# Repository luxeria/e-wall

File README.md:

e-wall
======

Steuerung e-wall

Die E-Wall ist eine Wand bestehend aus 12 Mainboards. 
Wenn Personen vor der Wand durchlaufen, soll darauf reagiert werden. 

Die Messung der Distanz erfolgt dabei über Ultraschall. 
Die Lüfter und LEDs werden mit einem Schieberegister angesteuert.

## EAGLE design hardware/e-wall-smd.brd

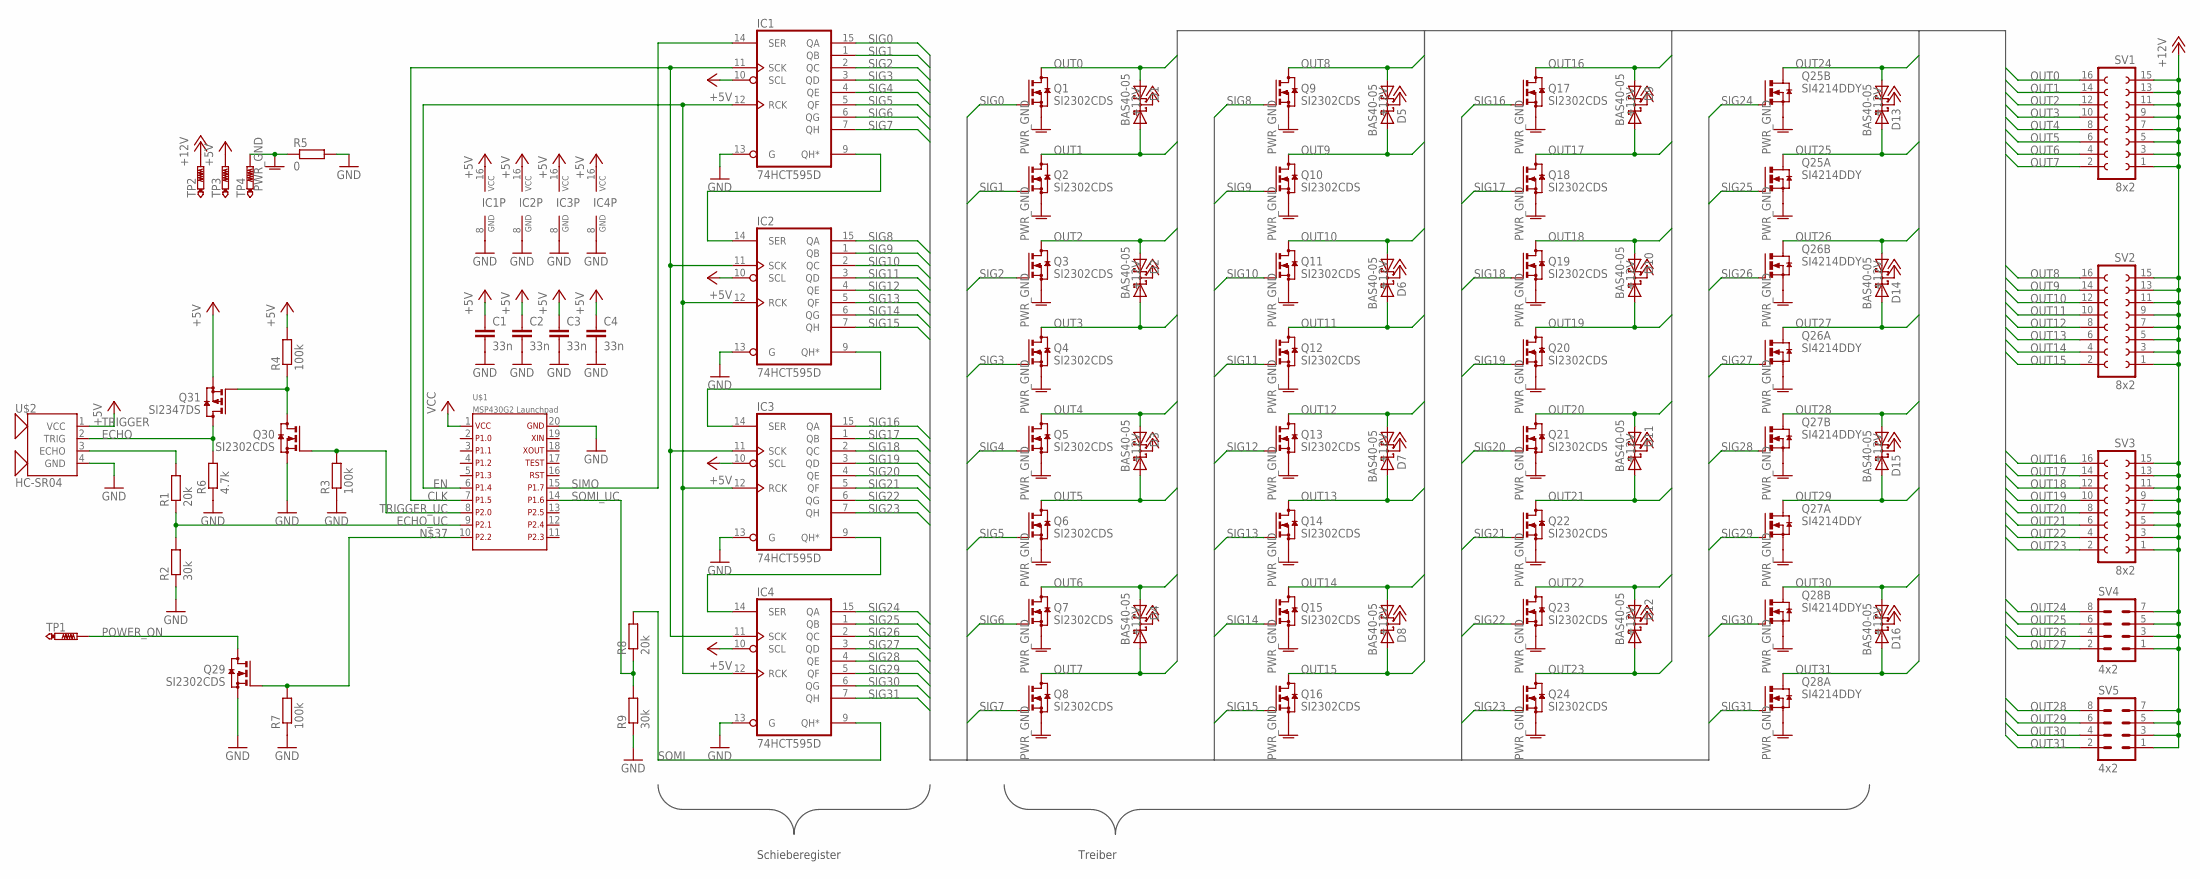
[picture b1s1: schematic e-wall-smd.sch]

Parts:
C1, C2, C3, C4: 33n; C1206
D1, D2, D3, D4, D5, D6, D7, D8, D9, D10, D11, D12, D13, D14, D15, D16: BAS40-05; SOT23
IC1, IC2, IC3, IC4: 74HCT595D; SO16
Q1, Q2, Q3, Q4, Q5, Q6, Q7, Q8, Q9, Q10, Q11, Q12, Q13, Q14, Q15, Q16, Q17, Q18, Q19, Q20, Q21, Q22, Q23, Q24, Q29, Q30: SI2302CDS; SOT23
Q25, Q26, Q27, Q28: SI4214DDY; SO-08
Q31: SI2347DS; SOT23
R1, R8: 20k; R1206
R2, R9: 30k; R1206
R3, R4, R7: 100k; R1206
R5: 0; R1206
R6: 4.7k; R1206
SV1, SV2, SV3: 8x2; FE08-2
SV4, SV5: 4x2; MA04-2
TP1, TP2, TP3, TP4: PTR1PAD1-20; P1-20
U$1: MSP430G2 Launchpad; MSP430LAUNCHPAD_BASIC
U$2: HC-SR04

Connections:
+5V: C1.1, C2.1, C3.1, C4.1, IC1.10 (SCL), IC1.16 (VCC), IC2.10 (SCL), IC2.16 (VCC), IC3.10 (SCL), IC3.16 (VCC), IC4.10 (SCL), IC4.16 (VCC), Q31.2 (S), R4.2, TP3.TP, U$2.1 (VCC)
+12V: D1.3 (C), D2.3 (C), D3.3 (C), D4.3 (C), D5.3 (C), D6.3 (C), D7.3 (C), D8.3 (C), D9.3 (C), D10.3 (C), D11.3 (C), D12.3 (C), D13.3 (C), D14.3 (C), D15.3 (C), D16.3 (C), SV1.1, SV1.3, SV1.5, SV1.7, SV1.9, SV1.11, SV1.13, SV1.15, SV2.1, SV2.3, SV2.5, SV2.7, SV2.9, SV2.11, SV2.13, SV2.15, SV3.1, SV3.3, SV3.5, SV3.7, SV3.9, SV3.11, SV3.13, SV3.15, SV4.1, SV4.3, SV4.5, SV4.7, SV5.1, SV5.3, SV5.5, SV5.7, TP2.TP
CLK: IC1.11 (SCK), IC2.11 (SCK), IC3.11 (SCK), IC4.11 (SCK), U$1.7
ECHO: R1.2, U$2.3 (ECHO)
ECHO_UC: R1.1, R2.2, U$1.9
EN: IC1.12 (RCK), IC2.12 (RCK), IC3.12 (RCK), IC4.12 (RCK), U$1.6
GND: C1.2, C2.2, C3.2, C4.2, IC1.8 (GND), IC1.13 (G), IC2.8 (GND), IC2.13 (G), IC3.8 (GND), IC3.13 (G), IC4.8 (GND), IC4.13 (G), Q29.2 (S), Q30.2 (S), R2.1, R3.1, R5.2, R6.1, R7.1, R9.1, U$1.20, U$2.4 (GND)
unnamed: IC1.9 (QH*), IC2.14 (SER)
unnamed: IC2.9 (QH*), IC3.14 (SER)
unnamed: IC3.9 (QH*), IC4.14 (SER)
unnamed: Q30.3 (D), Q31.1 (G), R4.1
unnamed: Q29.1 (G), R7.2, U$1.10
OUT0: D1.2 (A2), Q1.3 (D), SV1.16
OUT1: D1.1 (A1), Q2.3 (D), SV1.14
OUT2: D2.2 (A2), Q3.3 (D), SV1.12
OUT3: D2.1 (A1), Q4.3 (D), SV1.10
OUT4: D3.2 (A2), Q5.3 (D), SV1.8
OUT5: D3.1 (A1), Q6.3 (D), SV1.6
OUT6: D4.2 (A2), Q7.3 (D), SV1.4
OUT7: D4.1 (A1), Q8.3 (D), SV1.2
OUT8: D5.1 (A1), Q9.3 (D), SV2.16
OUT9: D5.2 (A2), Q10.3 (D), SV2.14
OUT10: D6.1 (A1), Q11.3 (D), SV2.12
OUT11: D6.2 (A2), Q12.3 (D), SV2.10
OUT12: D7.1 (A1), Q13.3 (D), SV2.8
OUT13: D7.2 (A2), Q14.3 (D), SV2.6
OUT14: D8.1 (A1), Q15.3 (D), SV2.4
OUT15: D8.2 (A2), Q16.3 (D), SV2.2
OUT16: D9.2 (A2), Q17.3 (D), SV3.16
OUT17: D9.1 (A1), Q18.3 (D), SV3.14
OUT18: D10.2 (A2), Q19.3 (D), SV3.12
OUT19: D10.1 (A1), Q20.3 (D), SV3.10
OUT20: D11.2 (A2), Q21.3 (D), SV3.8
OUT21: D11.1 (A1), Q22.3 (D), SV3.6
OUT22: D12.2 (A2), Q23.3 (D), SV3.4
OUT23: D12.1 (A1), Q24.3 (D), SV3.2
OUT24: D13.1 (A1), Q25.7 (D), Q25.8 (D), SV4.8
OUT25: D13.2 (A2), Q25.5 (D), Q25.6 (D), SV4.6
OUT26: D14.1 (A1), Q26.7 (D), Q26.8 (D), SV4.4
OUT27: D14.2 (A2), Q26.5 (D), Q26.6 (D), SV4.2
OUT28: D15.1 (A1), Q27.7 (D), Q27.8 (D), SV5.8
OUT29: D15.2 (A2), Q27.5 (D), Q27.6 (D), SV5.6
OUT30: D16.1 (A1), Q28.7 (D), Q28.8 (D), SV5.4
OUT31: D16.2 (A2), Q28.5 (D), Q28.6 (D), SV5.2
POWER_ON: Q29.3 (D), TP1.TP
PWR_GND: Q1.2 (S), Q2.2 (S), Q3.2 (S), Q4.2 (S), Q5.2 (S), Q6.2 (S), Q7.2 (S), Q8.2 (S), Q9.2 (S), Q10.2 (S), Q11.2 (S), Q12.2 (S), Q13.2 (S), Q14.2 (S), Q15.2 (S), Q16.2 (S), Q17.2 (S), Q18.2 (S), Q19.2 (S), Q20.2 (S), Q21.2 (S), Q22.2 (S), Q23.2 (S), Q24.2 (S), Q25.1 (S), Q25.3 (S), Q26.1 (S), Q26.3 (S), Q27.1 (S), Q27.3 (S), Q28.1 (S), Q28.3 (S), R5.1, TP4.TP
SIG0: IC1.15 (QA), Q1.1 (G)
SIG1: IC1.1 (QB), Q2.1 (G)
SIG2: IC1.2 (QC), Q3.1 (G)
SIG3: IC1.3 (QD), Q4.1 (G)
SIG4: IC1.4 (QE), Q5.1 (G)
SIG5: IC1.5 (QF), Q6.1 (G)
SIG6: IC1.6 (QG), Q7.1 (G)
SIG7: IC1.7 (QH), Q8.1 (G)
SIG8: IC2.15 (QA), Q9.1 (G)
SIG9: IC2.1 (QB), Q10.1 (G)
SIG10: IC2.2 (QC), Q11.1 (G)
SIG11: IC2.3 (QD), Q12.1 (G)
SIG12: IC2.4 (QE), Q13.1 (G)
SIG13: IC2.5 (QF), Q14.1 (G)
SIG14: IC2.6 (QG), Q15.1 (G)
SIG15: IC2.7 (QH), Q16.1 (G)
SIG16: IC3.15 (QA), Q17.1 (G)
SIG17: IC3.1 (QB), Q18.1 (G)
SIG18: IC3.2 (QC), Q19.1 (G)
SIG19: IC3.3 (QD), Q20.1 (G)
SIG20: IC3.4 (QE), Q21.1 (G)
SIG21: IC3.5 (QF), Q22.1 (G)
SIG22: IC3.6 (QG), Q23.1 (G)
SIG23: IC3.7 (QH), Q24.1 (G)
SIG24: IC4.15 (QA), Q25.2 (G)
SIG25: IC4.1 (QB), Q25.4 (G)
SIG26: IC4.2 (QC), Q26.2 (G)
SIG27: IC4.3 (QD), Q26.4 (G)
SIG28: IC4.4 (QE), Q27.2 (G)
SIG29: IC4.5 (QF), Q27.4 (G)
SIG30: IC4.6 (QG), Q28.2 (G)
SIG31: IC4.7 (QH), Q28.4 (G)
SIMO: IC1.14 (SER), U$1.15
SOMI: IC4.9 (QH*), R8.2
SOMI_UC: R8.1, R9.2, U$1.14
TRIGGER: Q31.3 (D), R6.2, U$2.2 (TRIG)
TRIGGER_UC: Q30.1 (G), R3.2, U$1.8
VCC: U$1.1

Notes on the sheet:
Treiber
Schieberegister

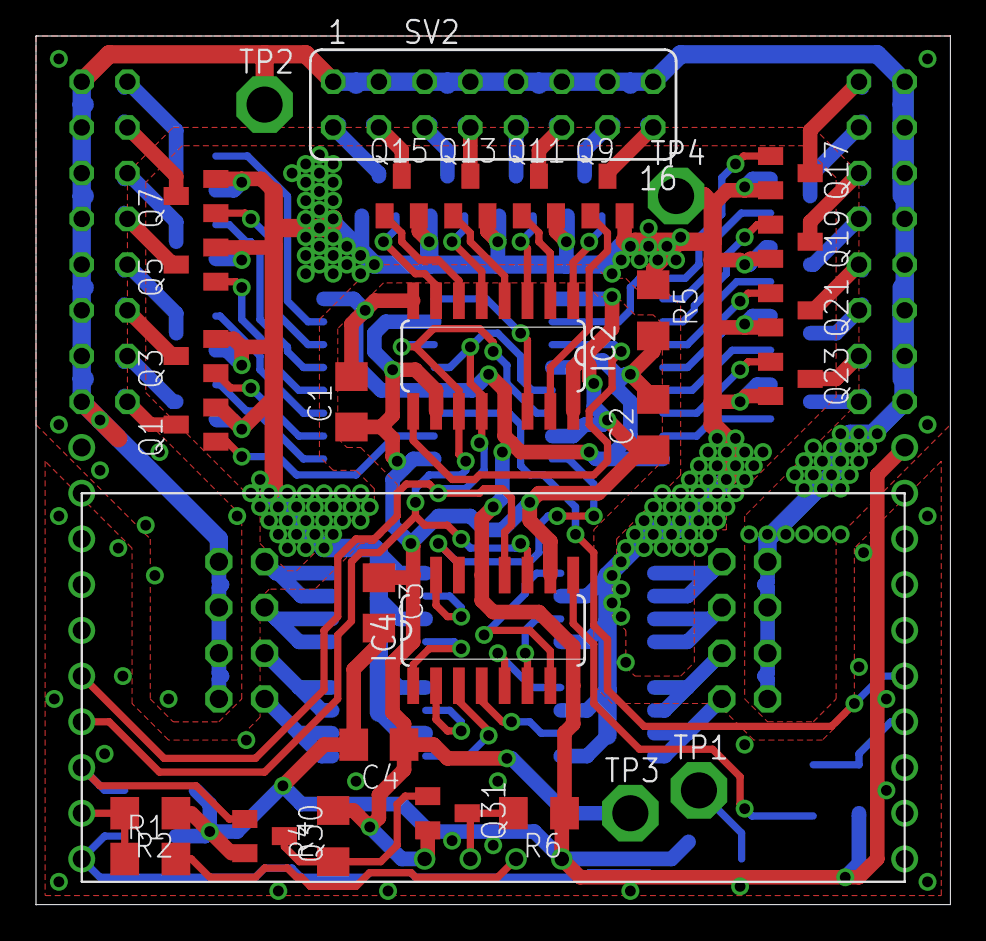
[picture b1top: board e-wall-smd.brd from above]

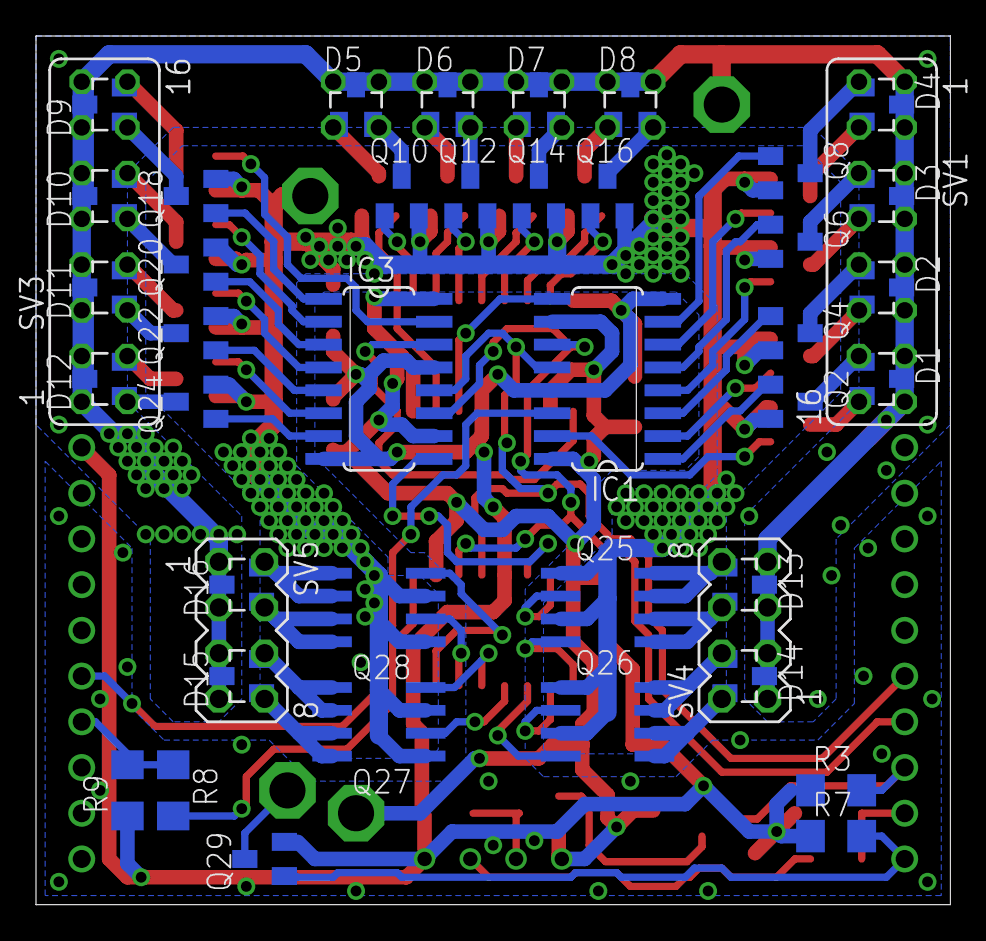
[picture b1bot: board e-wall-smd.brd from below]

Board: 2 copper layers, 50.8 x 48.3 mm, 75 parts (43 on the bottom side), 83 nets.

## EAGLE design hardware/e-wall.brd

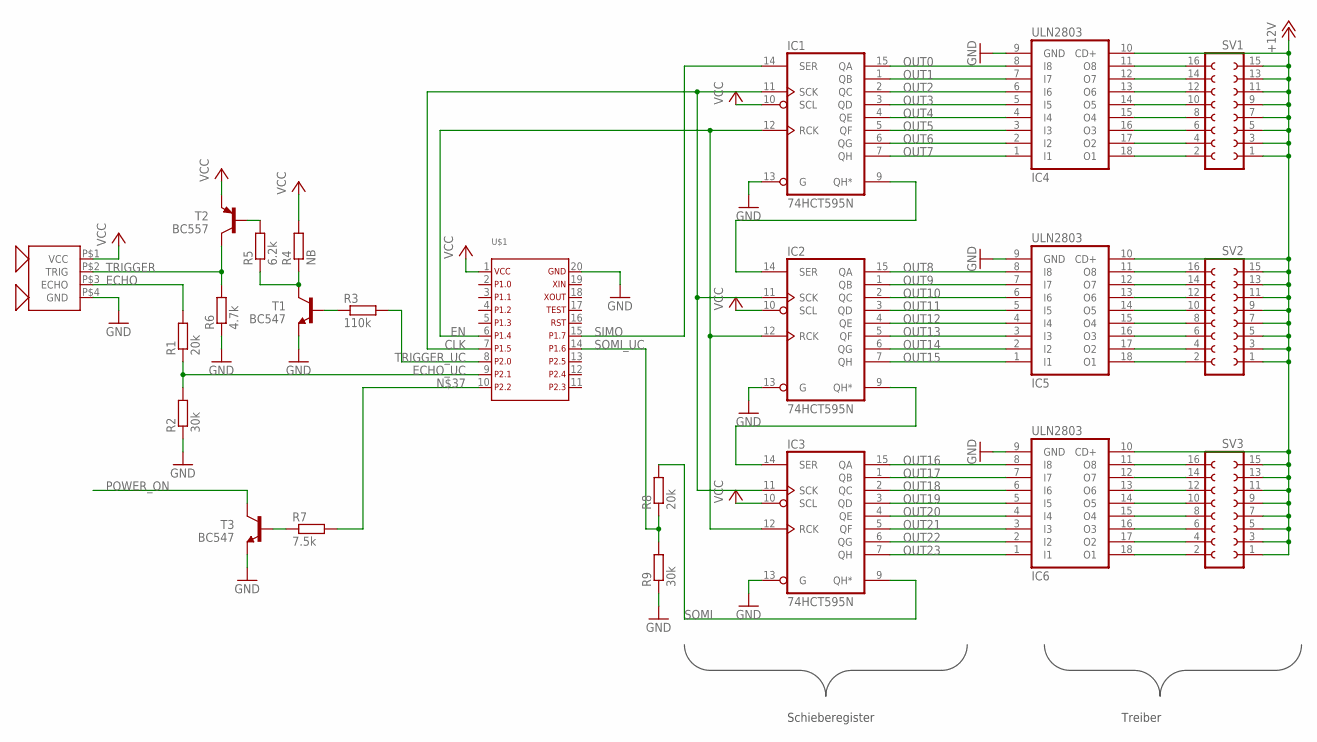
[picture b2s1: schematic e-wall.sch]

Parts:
IC1, IC2, IC3: 74HCT595N; DIL16
IC4, IC5, IC6: ULN2803; DIL18
R1, R8: 20k; 0207/7
R2, R9: 30k; 0207/7
R3: 110k; 0207/7
R4: NB; 0207/2V
R5: 6.2k; 0207/2V
R6: 4.7k; 0207/7
R7: 7.5k; 0207/7
SV1, SV2, SV3: FE08-2
T1, T3: BC547; TO92-EBC
T2: BC557; TO92-BEC
U$1: MSP430LAUNCHPAD_BASIC
U$2: HC-SR04

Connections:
+12V: IC4.10 (CD+), IC5.10 (CD+), IC6.10 (CD+), SV1.1, SV1.3, SV1.5, SV1.7, SV1.9, SV1.11, SV1.13, SV1.15, SV2.1, SV2.3, SV2.5, SV2.7, SV2.9, SV2.11, SV2.13, SV2.15, SV3.1, SV3.3, SV3.5, SV3.7, SV3.9, SV3.11, SV3.13, SV3.15
CLK: IC1.11 (SCK), IC2.11 (SCK), IC3.11 (SCK), U$1.7
ECHO: R1.2, U$2.P$3 (ECHO)
ECHO_UC: R1.1, R2.2, U$1.9
EN: IC1.12 (RCK), IC2.12 (RCK), IC3.12 (RCK), U$1.6
GND: IC1.8 (GND), IC1.13 (G), IC2.8 (GND), IC2.13 (G), IC3.8 (GND), IC3.13 (G), IC4.9 (GND), IC5.9 (GND), IC6.9 (GND), R2.1, R6.1, R9.1, T1.E, T3.E, U$1.20, U$2.P$4 (GND)
unnamed: IC1.9 (QH*), IC2.14 (SER)
unnamed: IC2.9 (QH*), IC3.14 (SER)
unnamed: IC6.18 (O1), SV3.2
unnamed: IC6.17 (O2), SV3.4
unnamed: IC6.16 (O3), SV3.6
unnamed: IC6.15 (O4), SV3.8
unnamed: IC6.14 (O5), SV3.10
unnamed: IC6.13 (O6), SV3.12
unnamed: IC6.12 (O7), SV3.14
unnamed: IC6.11 (O8), SV3.16
unnamed: IC5.18 (O1), SV2.2
unnamed: IC5.17 (O2), SV2.4
unnamed: IC5.16 (O3), SV2.6
unnamed: IC5.15 (O4), SV2.8
unnamed: IC5.14 (O5), SV2.10
unnamed: IC5.13 (O6), SV2.12
unnamed: IC5.12 (O7), SV2.14
unnamed: IC5.11 (O8), SV2.16
unnamed: IC4.18 (O1), SV1.2
unnamed: IC4.17 (O2), SV1.4
unnamed: IC4.16 (O3), SV1.6
unnamed: IC4.15 (O4), SV1.8
unnamed: IC4.14 (O5), SV1.10
unnamed: IC4.13 (O6), SV1.12
unnamed: IC4.12 (O7), SV1.14
unnamed: IC4.11 (O8), SV1.16
unnamed: R3.1, T1.B
unnamed: R4.1, R5.1, T1.C
unnamed: R5.2, T2.B
unnamed: R7.1, T3.B
unnamed: R7.2, U$1.10
OUT0: IC1.15 (QA), IC4.8 (I8)
OUT1: IC1.1 (QB), IC4.7 (I7)
OUT2: IC1.2 (QC), IC4.6 (I6)
OUT3: IC1.3 (QD), IC4.5 (I5)
OUT4: IC1.4 (QE), IC4.4 (I4)
OUT5: IC1.5 (QF), IC4.3 (I3)
OUT6: IC1.6 (QG), IC4.2 (I2)
OUT7: IC1.7 (QH), IC4.1 (I1)
OUT8: IC2.15 (QA), IC5.8 (I8)
OUT9: IC2.1 (QB), IC5.7 (I7)
OUT10: IC2.2 (QC), IC5.6 (I6)
OUT11: IC2.3 (QD), IC5.5 (I5)
OUT12: IC2.4 (QE), IC5.4 (I4)
OUT13: IC2.5 (QF), IC5.3 (I3)
OUT14: IC2.6 (QG), IC5.2 (I2)
OUT15: IC2.7 (QH), IC5.1 (I1)
OUT16: IC3.15 (QA), IC6.8 (I8)
OUT17: IC3.1 (QB), IC6.7 (I7)
OUT18: IC3.2 (QC), IC6.6 (I6)
OUT19: IC3.3 (QD), IC6.5 (I5)
OUT20: IC3.4 (QE), IC6.4 (I4)
OUT21: IC3.5 (QF), IC6.3 (I3)
OUT22: IC3.6 (QG), IC6.2 (I2)
OUT23: IC3.7 (QH), IC6.1 (I1)
POWER_ON: T3.C
SIMO: IC1.14 (SER), U$1.15
SOMI: IC3.9 (QH*), R8.2
SOMI_UC: R8.1, R9.2, U$1.14
TRIGGER: R6.2, T2.C, U$2.P$2 (TRIG)
TRIGGER_UC: R3.2, U$1.8
VCC: IC1.10 (SCL), IC1.16 (VCC), IC2.10 (SCL), IC2.16 (VCC), IC3.10 (SCL), IC3.16 (VCC), R4.2, T2.E, U$1.1, U$2.P$1 (VCC)

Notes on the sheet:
Treiber
Schieberegister

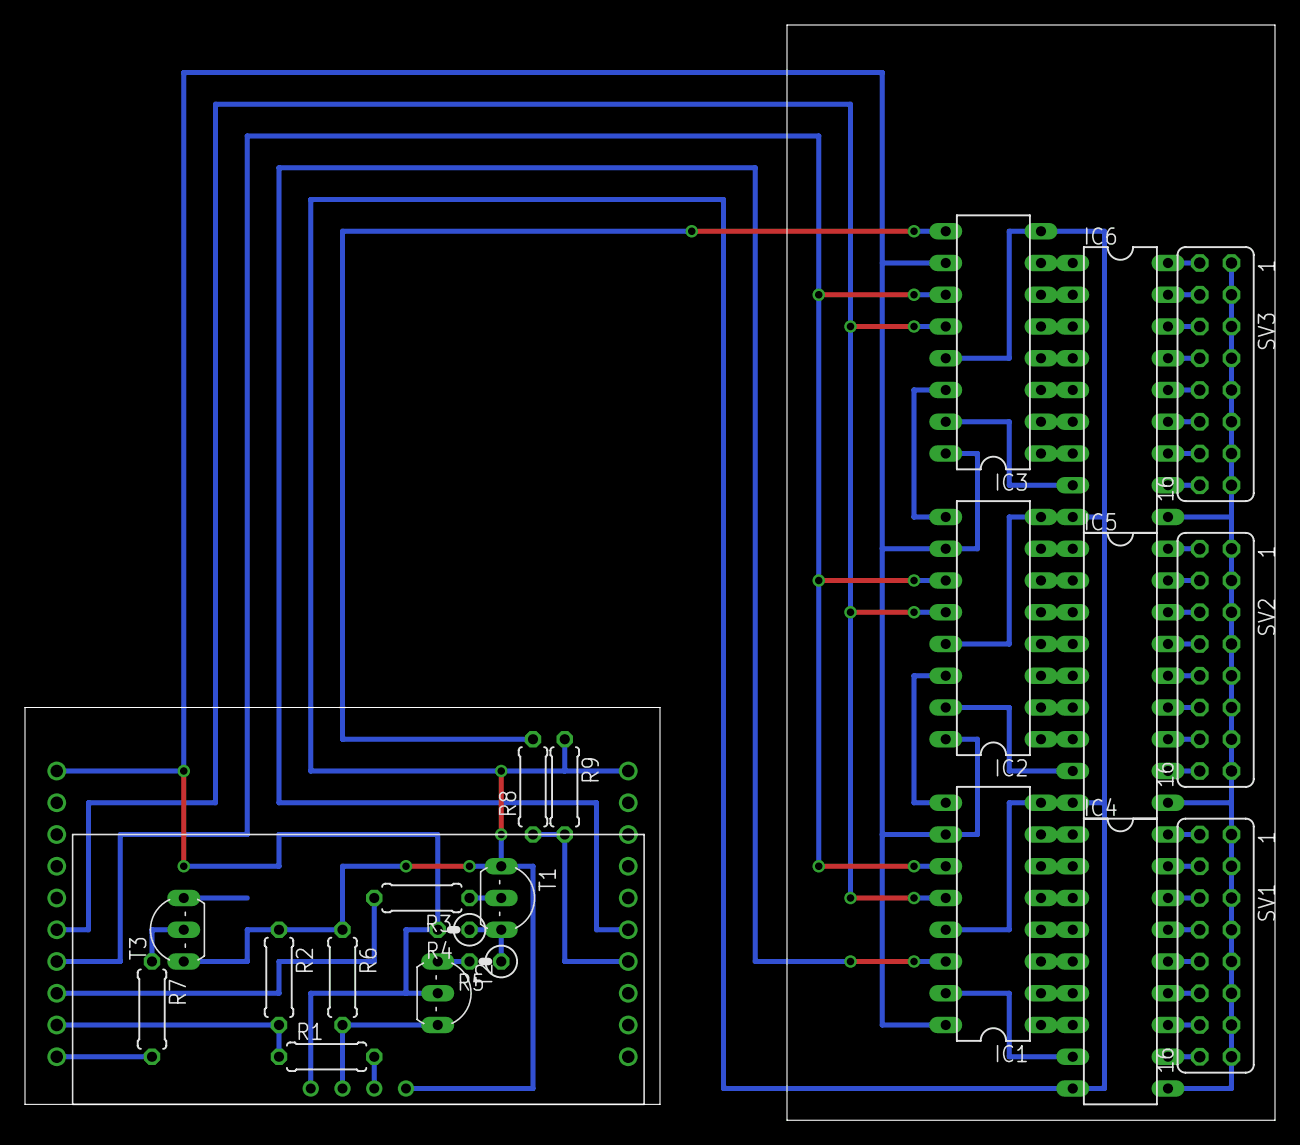
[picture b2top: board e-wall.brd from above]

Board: 2 copper layers, 100.0 x 87.6 mm, 23 parts (0 on the bottom side), 67 nets.

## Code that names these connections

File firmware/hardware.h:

#ifndef HARDWARE_H
#define HARDWARE_H

/**
 * @file
 *
 * Hardware description for the ti launchpad
 * Header file for hardware.c
 *
 * @author      Daniel Winz <daniel.winz@stud.hslu.ch>
 */

#include <msp430.h>
#include <stdint.h>

// - - - - - - - - - - - - - - - - - - - - - - - - - - - - - - - - - - - - - -


/*
PINS:
Comment-Abbreviations:
I: Input, O: Output (PxDIR)
M: Module (PxSEL)
L: Low, H: high (PxOut)
R: Pullup/down Resistor active (PxREN)
Comment
*/


//--- Watchdog Timer ---
#define WDTCTL_INIT     (WDTPW|WDTTMSEL|WDTCNTCL)   // Init watchdog as interval timer
#define IE1_WDT_INIT    (WDTIE)                     // Enable watchdog interrupt


//--- PORT1 ---
#define P1_0            BIT0    ///< |OL|       red LED for "Hello World"
#define P1_1            BIT1    ///< |IRL|      unused
#define P1_2            BIT2    ///< |IRL|      unused
#define P1_3            BIT3    ///< |IRL|      unused
#define P1_4            BIT4    ///< |OL|       Load for shift registers
#define P1_5            BIT5    ///< |OM|       SCK for shift registers
#define P1_6            BIT6    ///< |IM|       SOMI for shift registers
#define P1_7            BIT7    ///< |OM|       SIMO for shift registers

#define P1OUT_INIT      (P1_4)
#define P1SEL_INIT      (P1_5 | P1_6 | P1_7)
#define P1SEL2_INIT     (P1_5 | P1_6 | P1_7)
#define P1DIR_INIT      (P1_0 | P1_4)
#define P1REN_INIT      (P1_1 | P1_2 | P1_3)

#define P1IE_INIT       (0)     ///< disable irq
#define P1IES_INIT      (0)     ///< H->L transition


//--- PORT2 ---
#define P2_0            BIT0    ///< |OL|       Trigger for Ultrasonic distance modul
#define P2_1            BIT1    ///< |IM|       Echo for Ultrasonic distance modul
#define P2_2            BIT2    ///< |IRL|      unused
#define P2_3            BIT3    ///< |IRL|      unused
#define P2_4            BIT4    ///< |IRL|      unused
#define P2_5            BIT5    ///< |IRL|      unused
#define P2_6            BIT6    ///< |IRL|      unused
#define P2_7            BIT7    ///< |IRL|      unused


#define P2OUT_INIT      (0)
#define P2SEL_INIT      (P2_1)
#define P2SEL2_INIT     (0)
#define P2DIR_INIT      (P2_0)
#define P2REN_INIT      (P2_2 | P2_3 | P2_4 | P2_5 | P2_6 | P2_7)

#define CAPD_INIT       (0)

#define P2IE_INIT       (0)
#define P2IES_INIT      (0)


//--- PORT3 ---
#define P3_0            BIT0    ///< |IRL|      unused
#define P3_1            BIT1    ///< |IRL|      unused
#define P3_2            BIT2    ///< |IRL|      unused
#define P3_3            BIT3    ///< |IRL|      unused
#define P3_4            BIT4    ///< |IRL|      unused
#define P3_5            BIT5    ///< |IRL|      unused
#define P3_6            BIT6    ///< |IRL|      unused
#define P3_7            BIT7    ///< |IRL|      unused

//~ #define ADC_FLOW_INPUT  BIT5    ///< |IM|       ADC Channel of Flow Sensor input

#define P3OUT_INIT      (0)
#define P3SEL_INIT      (0)
#define P3DIR_INIT      (0)
#define P3REN_INIT      (P3_0 | P3_1 | P3_2 | P3_3 | P3_4 | P3_5 | P3_6 | P3_7)


//--- Interrupts ---
#define IE1_INIT        (0)
#define IE2_INIT        (0)


//~ //--- ADC ---
//~ #define ADC10CTL0_INIT  (ADC10SHT_3 | ADC10ON)
//~ #define ADC10CTL1_INIT  (INCH_5 | ADC10SSEL_3)
//~ #define ADC10AE0_INIT   (ADC_FLOW_INPUT)
//~ #define ADC10DTC0_INIT  (0)
//~ #define ADC10DTC1_INIT  (0)


//~ //--- Timer A ---
//~ #define TACTL_INIT      (TASSEL_2 | MC_1 | TACLR)
//~ #define TACCR0_INIT     (0xffff)
//~ #define TACCR1_INIT     (0x0)
//~ #define TACCTL1_INIT    (OUTMOD_7)


//~ //--- I2C ---
//~ #define I2C_ADDRESS     (0x49)                  // I2C Address
//~ #define UCB0CTL1_INIT_0 (UCSWRST)               // USCI reset
//~ #define UCB0CTL0_INIT   (UCMODE_3 | UCSYNC)     // 7-bit, single master, I2C, synchronous
                                                //~ // No need to configure UCB0CTL1, UCB0BR, nor UCB0I2CCSA for a slave
//~ #define UCB0I2COA_INIT  (I2C_ADDRESS)           // ignore genl call; own adress I2C_ADDRESS
//~ #define UCB0CTL1_INIT_1 (~UCSWRST)              // release from reset
//~ #define UCB0I2CIE_INIT  (UCSTTIE | UCSTPIE)     //enable interrupts on Start , Stop
//~ #define IE2_I2C_INIT    (UCB0RXIE | UCB0TXIE)   //enable interrupts on RX and TX


//~ //--- Clock Module ---
#define DCOCTL_INIT     (CALDCO_1MHZ)          
#define BCSCTL1_INIT    (XT2OFF|CALBC1_1MHZ)   
#define BCSCTL2_INIT    (0)                     
#define BCSCTL3_INIT    (0)                     


// - - - - - - - - - - - - - - - - - - - - - - - - - - - - - - - - - - - - - -


// function prototypes
void hardware_lowlevel_init(void);              // Initialize hardware

#endif //HARDWARE_H

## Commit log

2013-04-18 Initial Documentation
2013-04-18 .gitignore
2013-04-18 Arbeit an Doku
2013-04-19 Kopfzeile angepasst
2013-04-19 Konzept
2013-04-19 Anforderungen
2013-04-21 Blockschaltbild
2013-07-25 Hello World auf dem MSP430 Launchpad
2013-07-25 eagle library for msp430 from texas instruments (slac060e)
2013-07-25 temporäre Eagle Dateien eingetragen
2013-07-25 Bibliothek zu MSP430 Launchpad erstellt
2013-07-25 Pinnummerierung korrigiert
2013-07-27 Schema angefangen
2013-07-29 LED und Lüfter im Blockschaltbild ergänzt
2013-07-29 typo
2013-07-29 Blockschaltbild ergänzt
2013-07-29 Detailkonzept angefangen
2013-07-29 Detailkonzept Distanzmessung
2013-07-30 Timingdiagramm zu Distanzmessung
2013-07-30 Timingdiagramm Distanzmessung: Flanken korrigiert
2013-07-30 label und caption zum Timingdiagramm hinzugefügt
2013-07-31 Deteilkonzept Ansteuerung Lüfter / LED
2013-07-31 Detailkonzept Speisung
2013-07-31 Ergänzung zu Detailkonzept Ansteuerung Lüfter / LED
2013-07-31 Anforderungen erweitert
2013-08-04 Detailkonzept Mikrocontroller
2013-08-05 Ergänzung zu Schieberegister
2013-08-06 Schieberegister für LEDs und Lüfter
2013-08-07 Technologie der Schieberegister von 74HC zu 74HCT geändert
2013-08-08 Wechsel zu 74HCT begründet
2013-08-09 Treiber für LED und Lüfter
2013-08-09 Blöcke angeschrieben
2013-08-10 Pegelwandler für Ultraschallsensor gezeichnet, aber noch nicht dimensioniert
2013-08-12 Ordner für Datenblätter in .gitignore eingetragen
2013-08-12 Pegelwandler in der Dokumentation ergänzt
2013-08-12 Pegelwandler mit zwei Transistoren
2013-08-15 hardware.h an Schema angepasst
2013-08-18 Skript für Datenblätter
2013-08-18 datasheets.sh korrogiert (windows Zeilenende zu Linux Zeilenende)
2013-08-19 Launchpad angeschrieben
2013-08-20 Dimensionierung angefangen
2013-08-21 Dimensionierung Pegelwandler Echo
2013-08-21 Dimensionierung Pegelwandler Echo berechnet
2013-08-22 Werte für Spannungsteiler
2013-08-23 Pegelwandler für Trigger korrigiert
2013-08-24 Dimensionierung Pegelwandler Trigger
2013-08-24 Bauteilwerte Pegelwandler Trigger
2013-08-24 Temporäre Dateien von vim in .gitignore eingetragen
2013-08-24 Datenblatt und Family Guide MSP430G2553
2013-08-25 74HC Family Specification
2013-08-25 74HC <-> 74HCT
2013-08-26 Transistoren beschriftet
2013-08-27 Beschreibung im Readme
2013-08-27 Pin Initialisierung für Echo korrigiert
2013-08-29 Projektname im makefile angepasst
2013-08-29 Temporäre Dateien des mspgcc im .gitignore eingetragen
2013-08-30 Schaltung Netzteileinschaltung
2013-08-31 Einschaltung der Speisung in der Doku ergänzt
2013-09-01 Kapitel Firmware
2013-09-02 Konzept Firmware angefangen
2013-09-03 Konzept Firmware
2014-04-20 ereutes herunterladen von bereits vorhandenen Datenblättern unterdrückt
2014-04-20 Toter Link zum Datenblatt vom 74HC595 ersetzt.
2014-04-21 Transistoren BSS123 durch Transistorarrays ULN2803 ersetzt
2014-04-21 Datenblatt ULN2803A
2014-04-21 Datenblätter der Bipolartransistoren
2014-04-22 SMD Bauteile durch THT ersetzt
2014-04-22 Layout erstellt
2014-07-08 Spannungsteiler für SOMI
2014-07-09 Datenblatt Ultraschallsensor
2014-07-09 Bauteil für Ultraschallsensor
2014-07-09 Ultraschallsensor eingebaut
2014-07-10 Package der Widerstände geändert
2014-07-10 SMD Version
2014-07-10 Freilaufdiode ergänzt
2014-07-11 Schieberegister verschoben
2014-07-13 Datenblatt 2N7002P
2014-07-15 Leitungen für SPI umbenannt
2014-07-18 Zusätzliches Schieberegister mit Treiber für mehr Strom
2014-07-18 Anschlüsse für Versorgung und Kupferflächen für MAsse und 12V
2014-07-20 Kleine anpassungen im Layout
2014-07-28 Pegelwandler mit FET
2014-07-28 Transistortypen festgelegt
2014-07-29 kleine Anpassungen im Schema, erc bereinigt
2014-07-30 Kondensatoren ergänzt
2014-07-30 Freilaufdioden bei Hochstromausgängen
2014-07-31 Design Rules von Platinensammler angewendet
2014-08-06 input anstelle von include
2014-09-01 Nicht benötigter Code entfernt
2014-09-02 Some typedefs and function prototypes
2014-09-04 datatypes changed to uintx_t
2014-09-16 state machine for ultrasonic measurement
2014-09-28 Some work on isr for ultrasonic module
2014-10-15 polygons prepared for additional cpooer wire
2014-10-16 moved some tracers to avoid layer change of high current paths
2014-10-18 Separate polygons for signal and power ground
2014-10-20 Polygons for adding copper wire to increase maximal current
2014-11-12 OSHW Logo
2014-11-12 Connections labled
2014-11-13 kleine Änderungen am Layout
2014-11-18 Small changes in ultrasonic
